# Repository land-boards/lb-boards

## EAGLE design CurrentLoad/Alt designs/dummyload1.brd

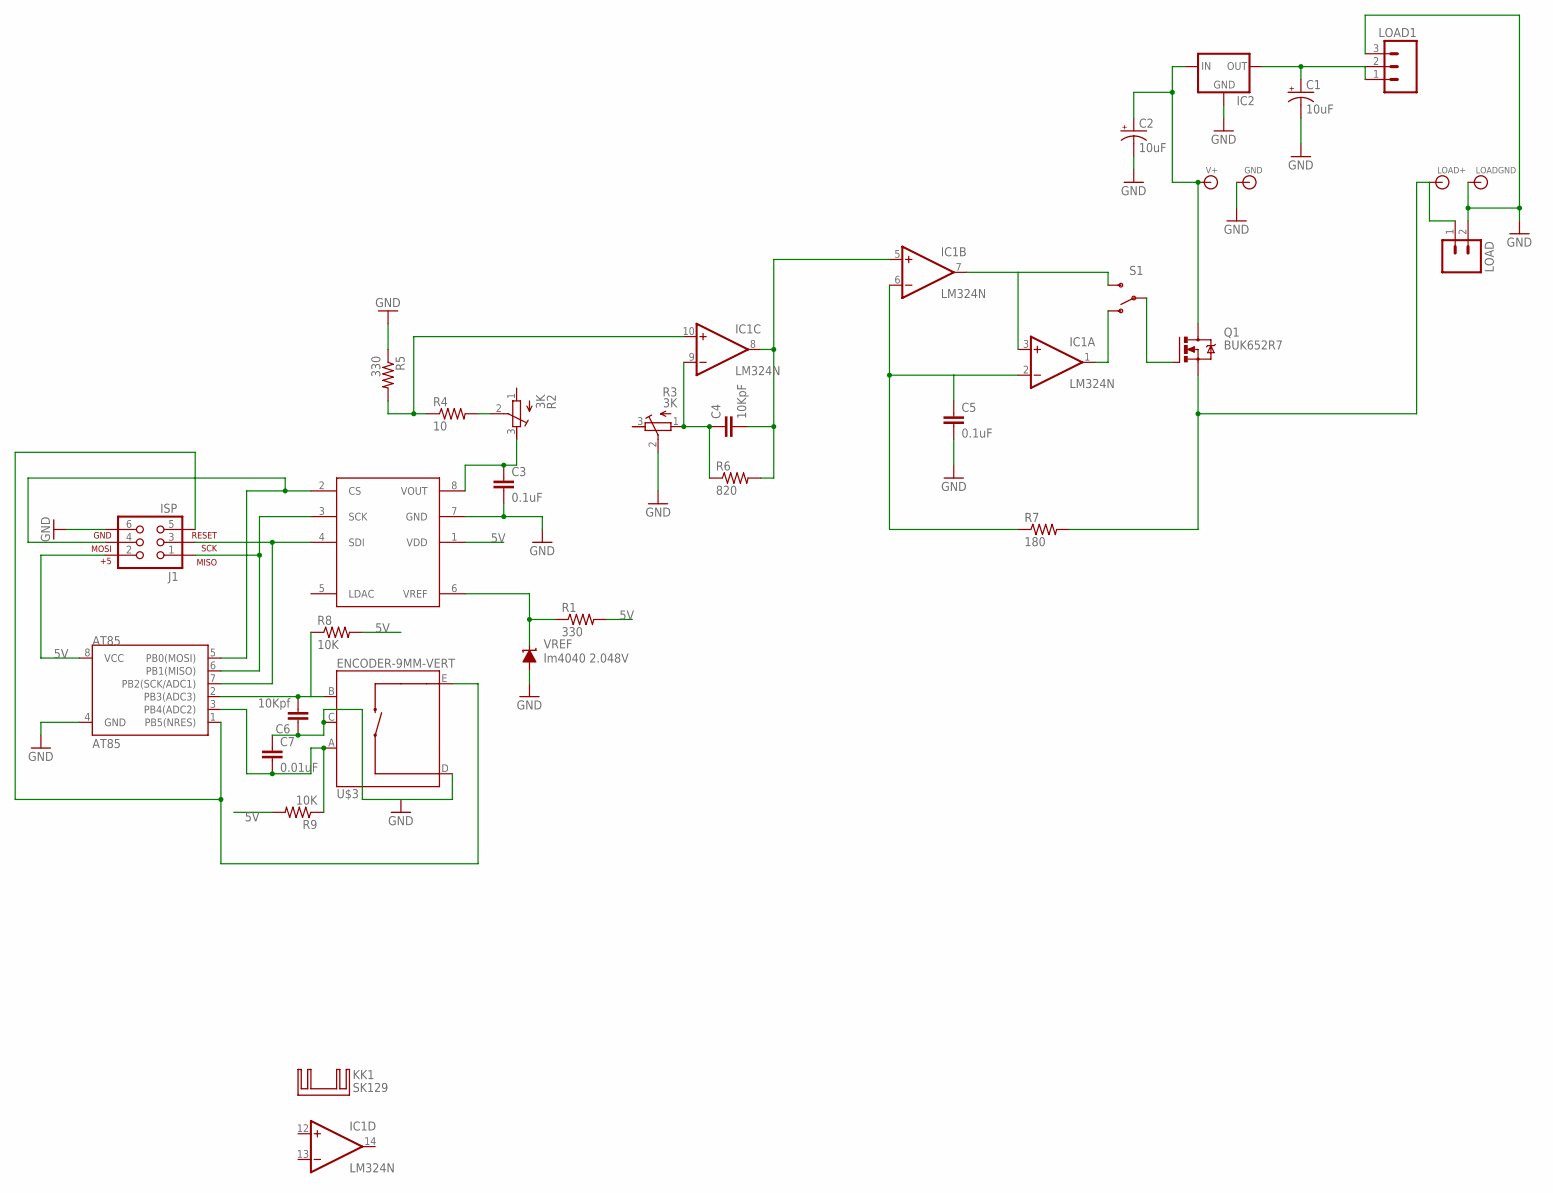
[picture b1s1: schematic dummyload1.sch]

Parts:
AT85: AT85; DIP08
C1, C2: 10uF; CPOL-RADIAL-10UF-25V
C3, C5: 0.1uF; CAP-PTH-SMALL2
C4: 10KpF; CAP-PTH-SMALL2
C6: 10Kpf; CAP-PTH-SMALL2
C7: 0.01uF; CAP-PTH-SMALL2
GND: BANANA_CONN
IC1: LM324N; DIL14
IC2: V_REG_78XXSINK; TO220-IGO
J1: ISP; 2X3-NS
KK1: SK129; SK129-HOLE
LOAD: M02LOCK; 1X02_LOCK
LOAD1: M031X03_NO_SILK; 1X03_NO_SILK
LOAD+: BANANA_CONN
LOADGND: BANANA_CONN
Q1: BUK652R7; TO220BV
R1, R5: 330; AXIAL-0.4
R2, R3: 3K; RTRIM3296W
R4: 10; AXIAL-0.4
R6: 820; AXIAL-0.4
R7: 180; AXIAL-0.4
R8, R9: 10K; AXIAL-0.4
S1: SWITCH-SPSTPTH; SWITCH-SPDT
U$2: MCP4921; DIL08
U$3: ENCODER-9MM-VERT; ENCODER-5PIN
V+: BANANA_CONN
VREF: lm4040 2.048V; LP_O-PBCY-W3

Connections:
5V: AT85.8 (VCC), C1.1 (+), IC2.OUT, J1.2, LOAD1.1, LOAD1.2, R1.P$2 (2), R8.P$2 (2), R9.P$2 (2), U$2.1 (VDD)
GND: AT85.4 (GND), C1.2 (-), C2.2 (-), C3.2, C5.2, C6.1, C7.1, GND.P$1, IC1.11 (V-), IC2.GND, J1.6, LOAD.2, LOAD1.3, LOADGND.P$1, R3.2 (S), R5.P$1 (1), U$2.7 (GND), U$3.C, U$3.D, VREF.3 (A)
unnamed: LOAD.1, LOAD+.P$1, Q1.S, R7.P$2 (2)
unnamed: AT85.5 (PB0(MOSI)), J1.4, U$2.2 (CS)
unnamed: IC1.1 (OUT), S1.1 (O)
unnamed: AT85.7 (PB2(SCK/ADC1)), J1.3, U$2.4 (SDI)
unnamed: R1.P$1 (1), U$2.6 (VREF), VREF.2 (C)
unnamed: C3.1, R2.3 (E), U$2.8 (VOUT)
unnamed: R2.2 (S), R4.P$2 (2)
unnamed: IC1.10 (+IN), R4.P$1 (1), R5.P$2 (2)
unnamed: C4.2, IC1.5 (+IN), IC1.8 (OUT), R6.P$2 (2)
unnamed: C4.1, IC1.9 (-IN), R3.1 (A), R6.P$1 (1)
unnamed: C5.1, IC1.2 (-IN), IC1.6 (-IN), R7.P$1 (1)
unnamed: IC1.3 (+IN), IC1.7 (OUT), S1.3 (S)
unnamed: AT85.1 (PB5(NRES)), J1.5, U$3.E
unnamed: Q1.G, S1.2
unnamed: AT85.3 (PB4(ADC2)), C7.2, R9.P$1 (1), U$3.A
unnamed: AT85.2 (PB3(ADC3)), C6.2, R8.P$1 (1), U$3.B
unnamed: AT85.6 (PB1(MISO)), J1.1, U$2.3 (SCK)
V+: C2.1 (+), IC1.4 (V+), IC2.IN, Q1.D, V+.P$1

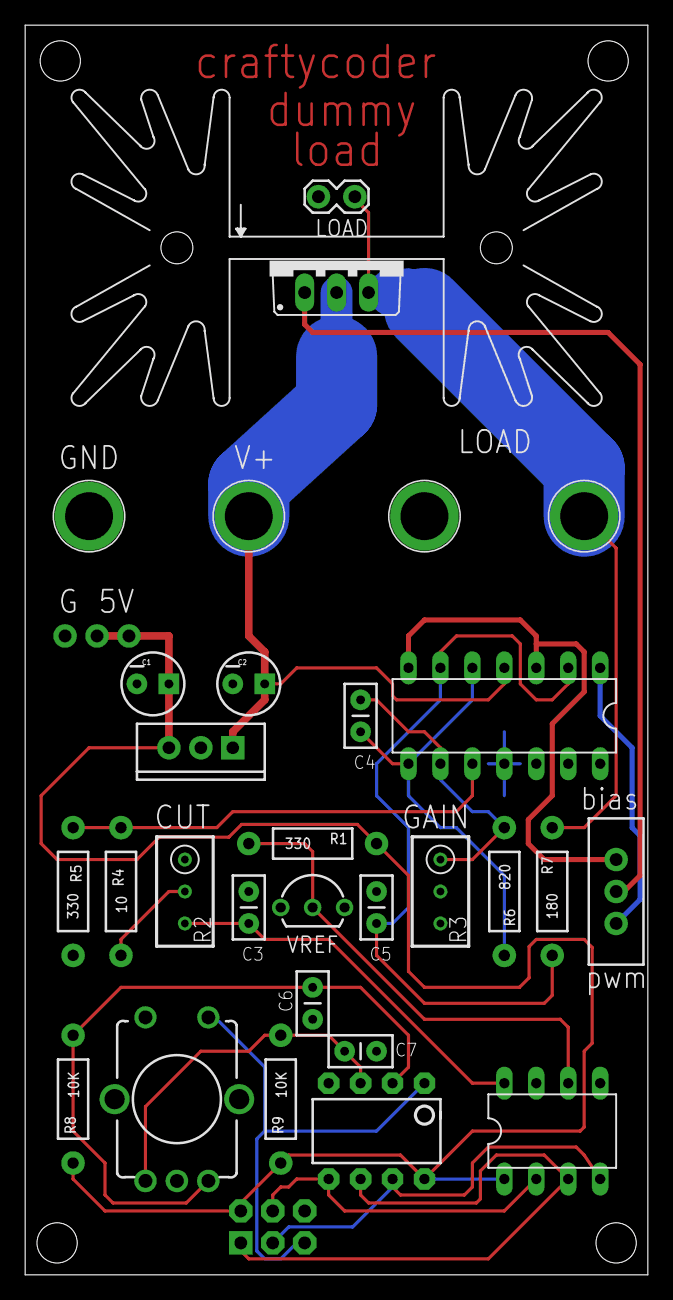
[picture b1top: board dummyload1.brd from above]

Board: 2 copper layers, 49.5 x 99.4 mm, 33 parts (0 on the bottom side), 20 nets.

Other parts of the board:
U$1: FREESIDELOGO-REVERSE

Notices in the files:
parts and their libraries:
SparkFun: Licensing: CC v3.0 Share-Alike You are welcome to use this library for commercial purposes.
